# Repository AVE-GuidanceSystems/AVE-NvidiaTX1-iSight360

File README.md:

# AVE-NvidiaTX1-iSight360
GPIO Breakout for iSight360

# Purpose
This PCB layout is intended to be for prototype purposes. This board fundamentally breaks out GPIO that is necessary for the iSight360 danger avoidence unit. Current build is limited to the layout and footprint size of the Development Carrier board provided by the Nvidia Jetson TX1. Future builds will include an all integrated carrier module to reduce overall footprint size.

Current build schematics are located under the PDFs folder. Schematics are found in the Schematics folder and Layout file is in the main directory along with project file and component banks.

# 3D Model

     - All 3-D models are in the designated folder

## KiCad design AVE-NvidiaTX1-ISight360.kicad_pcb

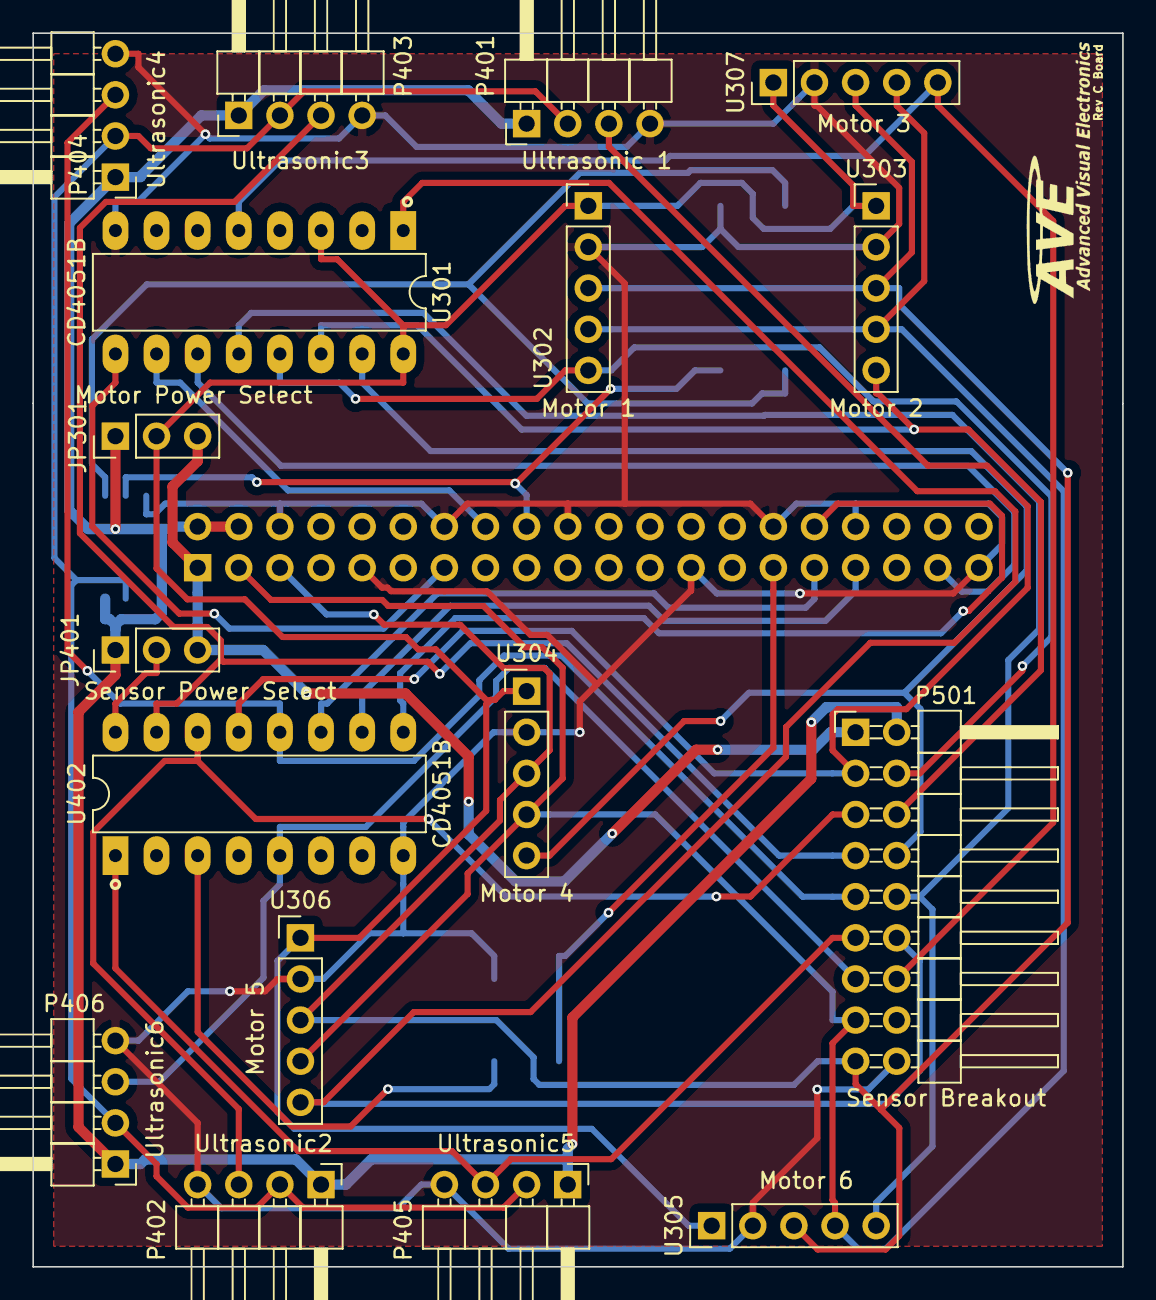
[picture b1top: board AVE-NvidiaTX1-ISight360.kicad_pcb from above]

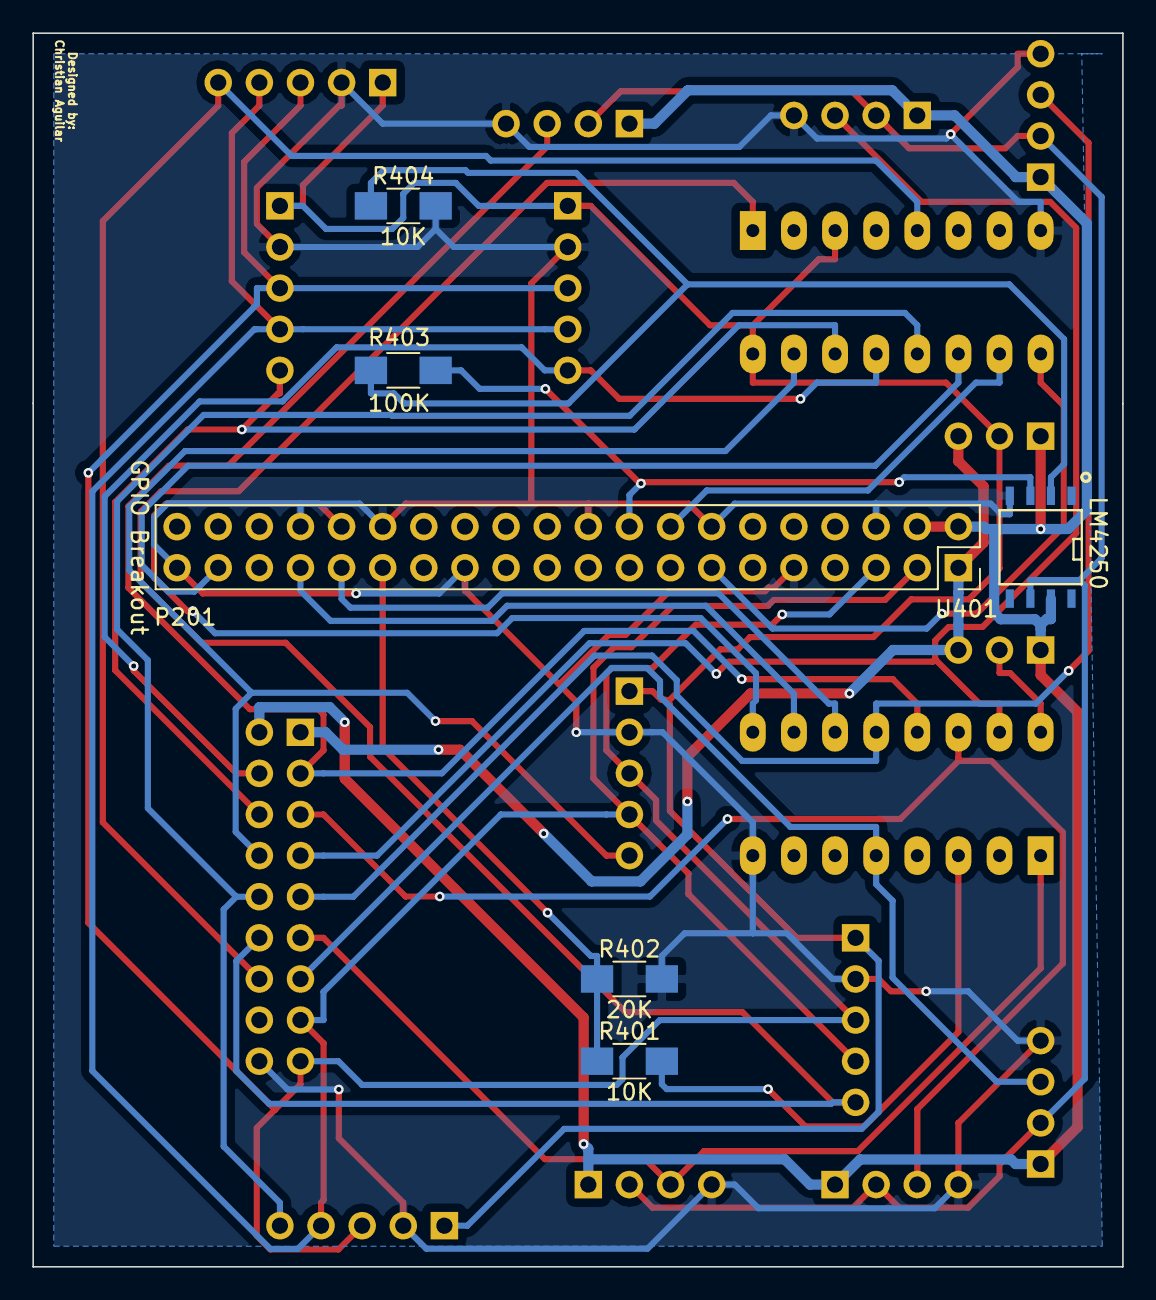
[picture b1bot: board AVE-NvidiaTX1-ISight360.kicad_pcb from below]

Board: 2 copper layers, 67.3 x 76.2 mm, 23 parts (6 on the bottom side), 30 nets.

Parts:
JP301: Motor Power Select; Pin_Header_Straight_1x03_Pitch2.54mm
JP401: Sensor Power Select; Pin_Header_Straight_1x03_Pitch2.54mm
P201: GPIO Breakout; Socket_Strip_Straight_2x20_Pitch2.54mm
P401: Ultrasonic 1; Pin_Header_Angled_1x04_Pitch2.54mm
P402: Ultrasonic2; Pin_Header_Angled_1x04_Pitch2.54mm
P403: Ultrasonic3; Pin_Header_Angled_1x04_Pitch2.54mm
P404: Ultrasonic4; Pin_Header_Angled_1x04_Pitch2.54mm
P405: Ultrasonic5; Pin_Header_Angled_1x04_Pitch2.54mm
P406: Ultrasonic6; Pin_Header_Angled_1x04_Pitch2.54mm
P501: Sensor Breakout; Pin_Header_Angled_2x09_Pitch2.54mm
R401, R404: 10K; R_1206_HandSoldering
R402: 20K; R_1206_HandSoldering
R403: 100K; R_1206_HandSoldering
U301, U402: CD4051B; DIP-16_W7.62mm_LongPads
U302: Motor 1; Socket_Strip_Straight_1x05_Pitch2.54mm
U303: Motor 2; Socket_Strip_Straight_1x05_Pitch2.54mm
U304: Motor 4; Socket_Strip_Straight_1x05_Pitch2.54mm
U305: Motor 6; Socket_Strip_Straight_1x05_Pitch2.54mm
U306: Motor 5; Socket_Strip_Straight_1x05_Pitch2.54mm
U307: Motor 3; Socket_Strip_Straight_1x05_Pitch2.54mm
U401: LM4250; SOIC-8-N

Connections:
/Echo1: P401.3, P501.3, U402.13
/Echo2: P402.3, P501.5, U402.14
/Echo3: P403.3, P501.7, U402.15
/Echo4: P404.3, P501.9, U402.12
/Echo5: P405.3, P501.11, U402.1
/Echo6: P406.3, P501.13, U402.5
/GPIO Breakout/3.3V: JP301.3, JP401.3, P201.1, P501.1
/GPIO Breakout/5V: JP301.1, JP401.1, P201.2, P201.4, P401.1, P402.1, P403.1, P404.1, P405.1, P406.1, P501.2, U401.7
/GPIO Breakout/GPIO36: P201.32, U402.9
/GPIO Breakout/GPIO37: P201.16, U301.10
/GPIO Breakout/GPIO38: P201.13, U301.9
/GPIO Breakout/GPIO63: P201.33, U402.10
/GPIO Breakout/GPIO186: P201.31, U402.11
/GPIO Breakout/GPIO187: P201.37, U301.11
/HapticMotorBank/M-Power: JP301.2, U301.3, U301.16, U302.1, U303.1, U304.1, U305.1, U306.1, U307.1
/Mtrigger1: P501.4, U301.13, U302.5
/Mtrigger2: P501.6, U301.14, U303.5
/Mtrigger3: P501.8, U301.15, U304.5
/Mtrigger4: P501.10, U301.12, U305.5
/Mtrigger5: P501.12, U301.1, U306.5
/Mtrigger6: P501.14, U301.5, U307.5
/SCL: P201.5, P501.17, U302.3, U303.3, U304.3, U305.3, U306.3, U307.3
/SDA: P201.3, P501.15, U302.4, U303.4, U304.4, U305.4, U306.4, U307.4
/Sensor_Input_Val: P201.29, R401.1, R402.1
/Sensor_Trigger: P201.18, R403.1, U401.3
/UltrasonicSensorBank/U-Power: JP401.2, U402.16
/UltrasonicTigger: P401.2, P402.2, P403.2, P404.2, P405.2, P406.2, U401.6
GND: P201.6, P201.9, P201.14, P201.20, P201.25, P201.30, P201.34, P201.39, P401.4, P402.4, P403.4, P404.4, P405.4, P406.4, P501.18, R402.2, R404.2, U301.8, U302.2, U303.2, U304.2, U305.2, U306.2, U307.2, U401.4, U402.8
unnamed: R401.2, U402.3
unnamed: R403.2, R404.1, U401.2

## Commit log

2017-03-16 README Fix
2017-03-16 Schematic Page Setting Updated
2017-03-16 Supplied Components to Ultrasonic bank
2017-03-16 Added Components to J20Header Breakout
2017-03-16 Added components
2017-03-17 Rev 1 Schematics
2017-03-17 Rev 1 - fix and PDFs
2017-03-31 added DRV breakout board to haptic motor bank schematic
2017-04-03 More GPIO Pins Available
2017-04-04 Updated PDFs
2017-04-10 Rev .99999 w/ Layout
2017-04-10 Removed Unnecessary Project Files
2017-04-10 Rearranged Schematic Files
2017-04-13 Reduced number of components
2017-04-13 Layout Done
    Minor Tweaks were made to Schematic
2017-04-13 Added 3d image to README
2017-04-15 Redesign - Rev B Board
    Smaller Board, more symmetric, will be more stable
2017-04-17 Rev C Update
2017-04-17 Rev C Final: PDFs, 3D Images, Silkscreens all updated
